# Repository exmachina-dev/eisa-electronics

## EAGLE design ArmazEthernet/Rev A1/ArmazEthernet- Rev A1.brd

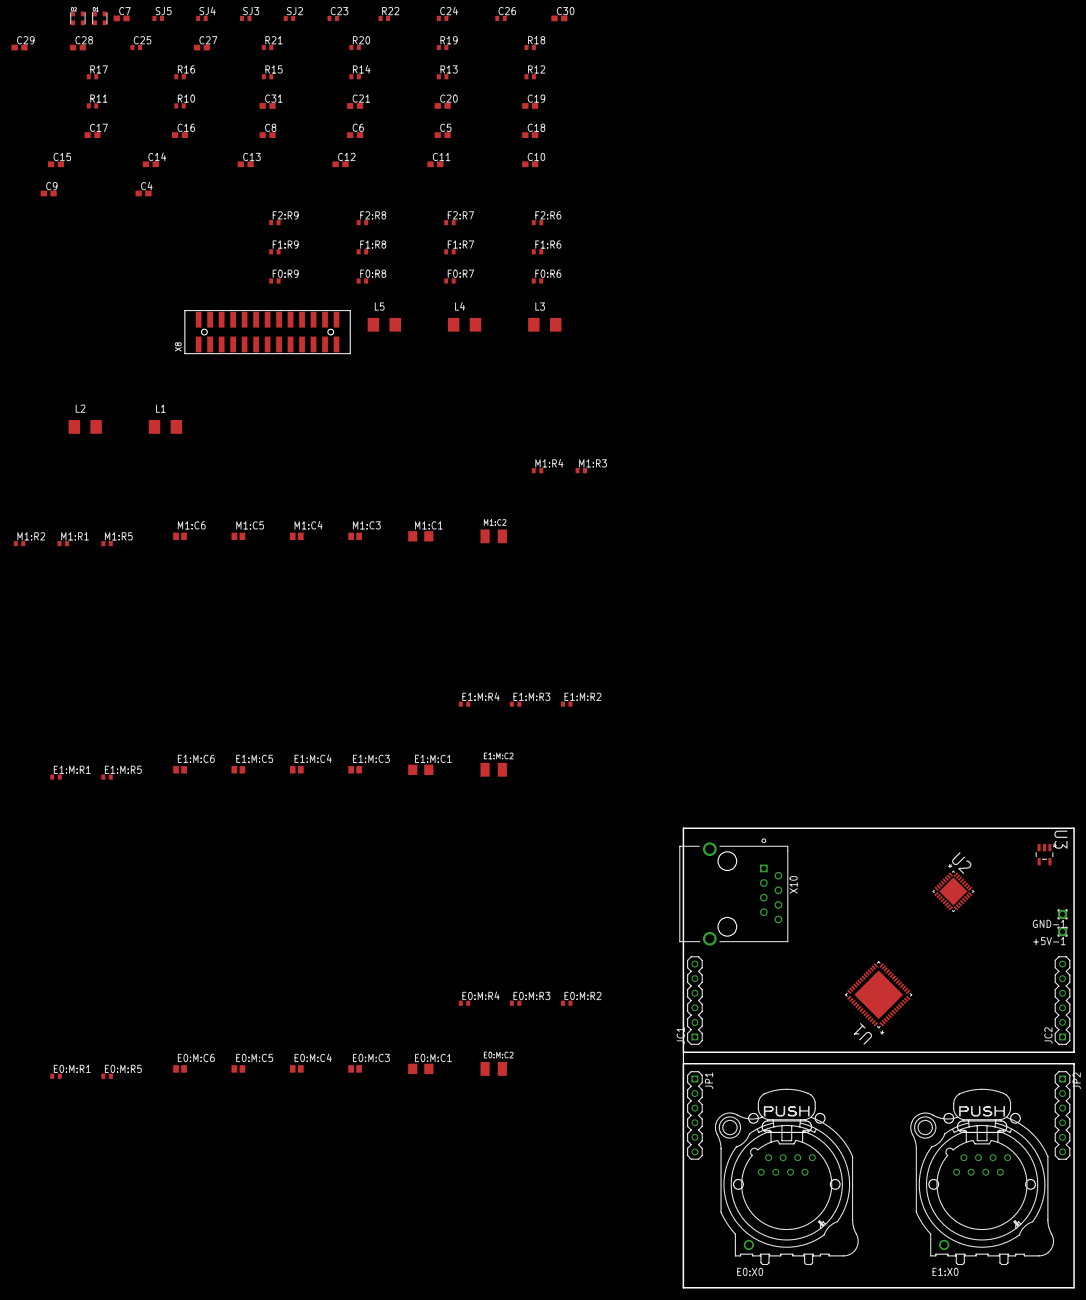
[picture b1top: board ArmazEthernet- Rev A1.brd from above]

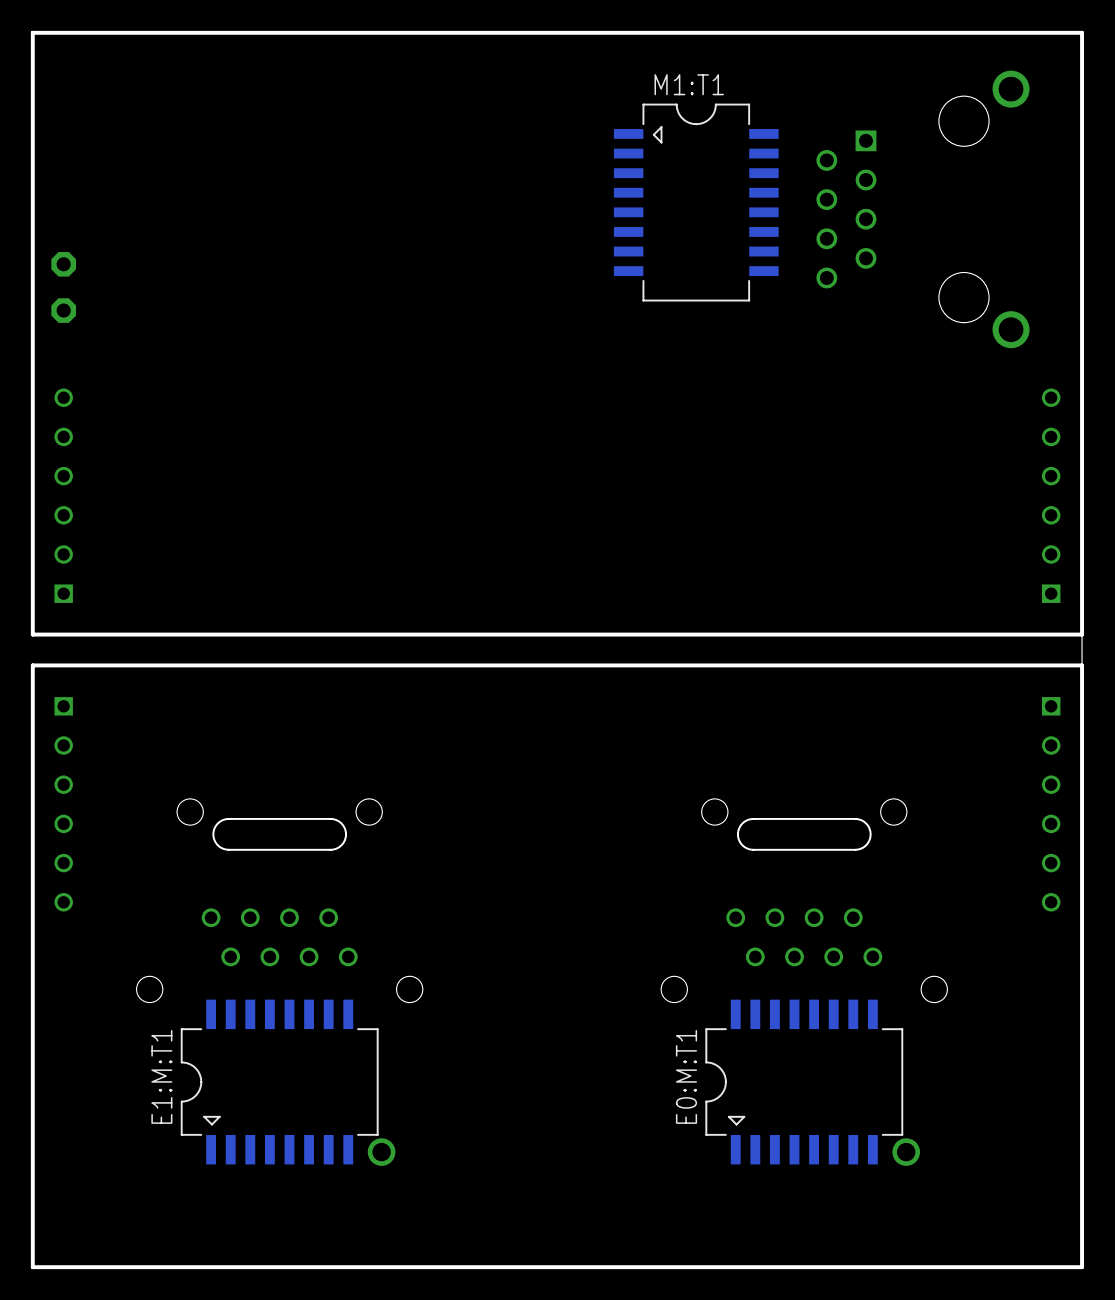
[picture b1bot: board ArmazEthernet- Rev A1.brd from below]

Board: 4 copper layers, 68.0 x 80.0 mm, 112 parts (3 on the bottom side), 92 nets, no tracks yet.

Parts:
+5V-1: WIREPAD1,6/0,9; 1,6/0,9
C4, C9, C10, C11, C12, C13, C14, C15, C18: 4.7uF, 6.3V, 20%; C0603
C5, C6, C8, C16, C17, C19, C20: 0.1uF, 16V, 10%; C0603
C7: 0.1uF; C0603
C21, C31: 0.01uF, 6V, 10%; C0603
C23: 1uF, 16V; C0402
C24: 10nF, 50V; C0402
C25: 4.7uF, 6.3V; C0402
C26: 0.1uF, 16V; C0402
C27: 4.7uF, 6.3V; C0603
C28, C29, C30: 0.1uF, 16V; C0603
E0:M:C1, E1:M:C1: 1000pF, 2kV; C1206
E0:M:C2, E1:M:C2: .022uF; SMC_B
E0:M:C3, E0:M:C4, E0:M:C5, E0:M:C6, E1:M:C3, E1:M:C4, E1:M:C5, E1:M:C6: 15pF, 50V; C0504
E0:M:R1, E0:M:R2, E0:M:R3, E0:M:R4, E1:M:R1, E1:M:R2, E1:M:R3, E1:M:R4: 75; R0402
E0:M:R5, E1:M:R5: 10, 1/8W, 1%; R0402
E0:M:T1, E1:M:T1: 749010012
E0:X0, E1:X0: NE8FAV
F0:R6, F0:R7, F0:R8, F0:R9, F1:R6, F1:R7, F1:R8, F1:R9, F2:R6, F2:R7, F2:R8, F2:R9: 49.9, 1/8W, 1%; R0402
GND-1: WIREPAD1,6/0,9; 1,6/0,9
JC1, JC2: 1X06
JP1, JP2: 1X06
L1, L2, L3, L4, L5: 2.0A/0.05 DCR; L4532M
M1:C1: 1000pF, 2kV; C1206
M1:C2: .022uF; SMC_B
M1:C3, M1:C4, M1:C5, M1:C6: 15pF, 50V; C0504
M1:R1, M1:R2, M1:R3, M1:R4: 75; R0402
M1:R5: 10, 1/8W, 1%; R0402
M1:T1: 749010012
O1, O2: 25MHz; ADSM
R10, R11, R12, R13, R14, R15, R16, R17, R18, R19, R20, R21: 10K, 1/10W, 1%; R0402
R22: 12K4, 1%; R0402
SJ2, SJ3, SJ4, SJ5: O, DNI; R0402
U1: LAN9303-ABZJ; QFN50P800X800X100-57N
U2: LAN8710AI-EZK; QFN50P500X500X100-33N
U3: LP2992IM5-3.3; SOT95P284X122-5N
X8: 87832-26
X10: 85505-5113; MOLEX_85505-5113

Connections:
+3V3: C4.1, C5.1, C6.1, C7.1, C8.1, C21.1, C25.1, C26.1, C31.1, L1.1, L2.1, L4.1, L5.1, O1.4, O2.4, R10.1, R12.1, R14.1, R16.1, R18.2, R19.2, R20.2, U1.9, U1.15, U1.23, U1.30, U1.32, U1.33, U3.5
+5V: +5V-1.1, C23.1, U3.1, U3.3, X8.1, X8.2
+12V: X8.21, X8.22
AVDD: C27.1, C28.1, C29.1, F2:R6.2, F2:R7.2, F2:R8.2, F2:R9.2, L5.2, M1:R5.2, U2.1, U2.27
DUPLEX_POL_0: R16.2, R17.1, SJ5.1
E0:M:N$1: E0:M:C2.+, E0:M:R5.1, E0:M:T1.2, E0:M:T1.7
E0:M:N$2: E0:M:R2.1, E0:M:T1.10
E0:M:N$3: E0:M:R4.1, E0:M:T1.15
E0:M:N$8: E0:M:C1.1, E0:M:R1.1, E0:M:R2.2, E0:M:R3.1, E0:M:R4.2
E0:N$1: E0:M:T1.11, E0:X0.1
E0:N$2: E0:M:T1.9, E0:X0.2
E0:N$3: E0:M:T1.16, E0:X0.3
E0:N$4: E0:M:T1.14, E0:X0.6
E0:N$5: E0:M:R1.2, E0:X0.4, E0:X0.5
E0:N$6: E0:M:R3.2, E0:X0.7, E0:X0.8
E1:M:N$1: E1:M:C2.+, E1:M:R5.1, E1:M:T1.2, E1:M:T1.7
E1:M:N$2: E1:M:R2.1, E1:M:T1.10
E1:M:N$3: E1:M:R4.1, E1:M:T1.15
E1:M:N$8: E1:M:C1.1, E1:M:R1.1, E1:M:R2.2, E1:M:R3.1, E1:M:R4.2
E1:N$1: E1:M:T1.11, E1:X0.1
E1:N$2: E1:M:T1.9, E1:X0.2
E1:N$3: E1:M:T1.16, E1:X0.3
E1:N$4: E1:M:T1.14, E1:X0.6
E1:N$5: E1:M:R1.2, E1:X0.4, E1:X0.5
E1:N$6: E1:M:R3.2, E1:X0.7, E1:X0.8
E2_1: M1:T1.11, X10.1
E2_2: M1:T1.9, X10.2
E2_3: M1:T1.16, X10.3
E2_4/5: M1:R1.2, X10.4, X10.5
E2_6: M1:T1.14, X10.6
E2_7/8: M1:R3.2, X10.7, X10.8
EE_SCL/SCL: R18.1, U1.36
EE_SDA/SDA: R19.1, U1.35
GND: C4.2, C5.2, C6.2, C7.2, C8.2, C9.2, C10.2, C11.2, C12.2, C13.2, C14.2, C15.2, C16.2, C17.2, C18.2, C19.2, C20.2, C21.2, C23.2, C24.2, C25.2, C26.2, C27.2, C28.2, C29.2, C30.2, C31.2, E0:M:C1.2, E0:M:C2.-, E0:M:C3.2, E0:M:C4.2, E0:M:C5.2, E0:M:C6.2, E0:X0.G, E1:M:C1.2, E1:M:C2.-, E1:M:C3.2, E1:M:C4.2, E1:M:C5.2, E1:M:C6.2, E1:X0.G, GND-1.1, JC1.6, JC2.6, JP1.6, JP2.6, M1:C1.2, M1:C2.-, M1:C3.2, M1:C4.2, M1:C5.2, M1:C6.2, O1.2, O2.2, R21.1, R22.1, SJ2.2, SJ3.2, SJ4.2, SJ5.2, U1.34, U1.57, U3.2, X8.3, X8.4, X10.M1, X10.M2
GND1: X8.25, X8.26
M1:N$1: M1:C2.+, M1:R5.1, M1:T1.2, M1:T1.7
M1:N$2: M1:R2.1, M1:T1.10
M1:N$3: M1:R4.1, M1:T1.15
M1:N$8: M1:C1.1, M1:R1.1, M1:R2.2, M1:R3.1, M1:R4.2
MDC: R21.2, U1.22, U2.17
MDIO: R20.1, U1.21, U2.16
unnamed: C24.1, U3.4
unnamed: R22.2, U1.49
unnamed: E0:M:C5.1, E0:M:T1.6, JP1.2
unnamed: E0:M:C6.1, E0:M:T1.8, JP1.3
unnamed: E0:M:C3.1, E0:M:T1.1, JP1.4
unnamed: E0:M:C4.1, E0:M:T1.3, JP1.5
unnamed: E1:M:R5.2, JP2.1
unnamed: E0:M:R5.2, JP1.1
unnamed: E1:M:C5.1, E1:M:T1.6, JP2.2
unnamed: E1:M:C6.1, E1:M:T1.8, JP2.3
unnamed: E1:M:C3.1, E1:M:T1.1, JP2.4
unnamed: E1:M:C4.1, E1:M:T1.3, JP2.5
P0_COL: U1.18, U2.15
P0_CRS: U1.19, U2.14
P0_INCLK: U1.8, U2.7
P0_IND0: U1.5, U2.11
P0_IND1: U1.4, U2.10
P0_IND2: U1.3, U2.9
P0_IND3: U1.2, U2.8
P0_INDV: U1.6, U2.26
P0_INER: U1.7, U2.13
P0_MODE0: R10.2, R11.1, SJ2.1
P0_MODE2: R14.2, R15.1, SJ4.1
P0_OUTCLK: U1.17, U2.20
P0_OUTD0/P0_MODE0: R11.2, U1.14, U2.22
P0_OUTD1/P0_MODE1: R13.2, U1.13
P0_OUTD2/P0_MODE2: R15.2, U1.12, U2.24
P0_OUTD3/DUPLEX_POL_0: R17.2, U1.11, U2.25
P0_OUTDV: U1.16, U2.21
PO_MODE1: R12.2, R13.1, SJ3.1
RXN0: F2:R9.1, M1:C4.1, M1:T1.3, U2.30
RXN1: F0:R9.1, JC1.5, U1.45
RXN2: F1:R9.1, JC2.5, U1.54
RXP0: F2:R8.1, M1:C3.1, M1:T1.1, U2.31
RXP1: F0:R8.1, JC1.4, U1.46
RXP2: F1:R8.1, JC2.4, U1.53
TXN0: F2:R7.1, M1:C6.1, M1:T1.8, U2.28
TXN1: F0:R7.1, JC1.3, U1.42
TXN2: F1:R7.1, JC2.3, U1.1
TXP0: F2:R6.1, M1:C5.1, M1:T1.6, U2.29
TXP1: F0:R6.1, JC1.2, U1.43
TXP2: F1:R6.1, JC2.2, U1.56
VDD18CORE: C15.1, C16.1, C17.1, L3.1, U1.10, U1.31
VDD18PLL: C13.1, L3.2, U1.41
VDD18TX: C18.1, C19.1, C20.1, U1.48, U1.51
VDD33A1: C9.1, C10.1, F0:R6.2, F0:R7.2, F0:R8.2, F0:R9.2, JC1.1, L1.2, U1.44, U1.47
VDD33A2: C11.1, C12.1, F1:R6.2, F1:R7.2, F1:R8.2, F1:R9.2, JC2.1, L2.2, U1.52, U1.55
VDD33BIAS: C14.1, L4.2, U1.50
VDDIO: C30.1, U2.12
XI: O1.3, U1.39
XTAL1/CLKIN: O2.3, U2.5

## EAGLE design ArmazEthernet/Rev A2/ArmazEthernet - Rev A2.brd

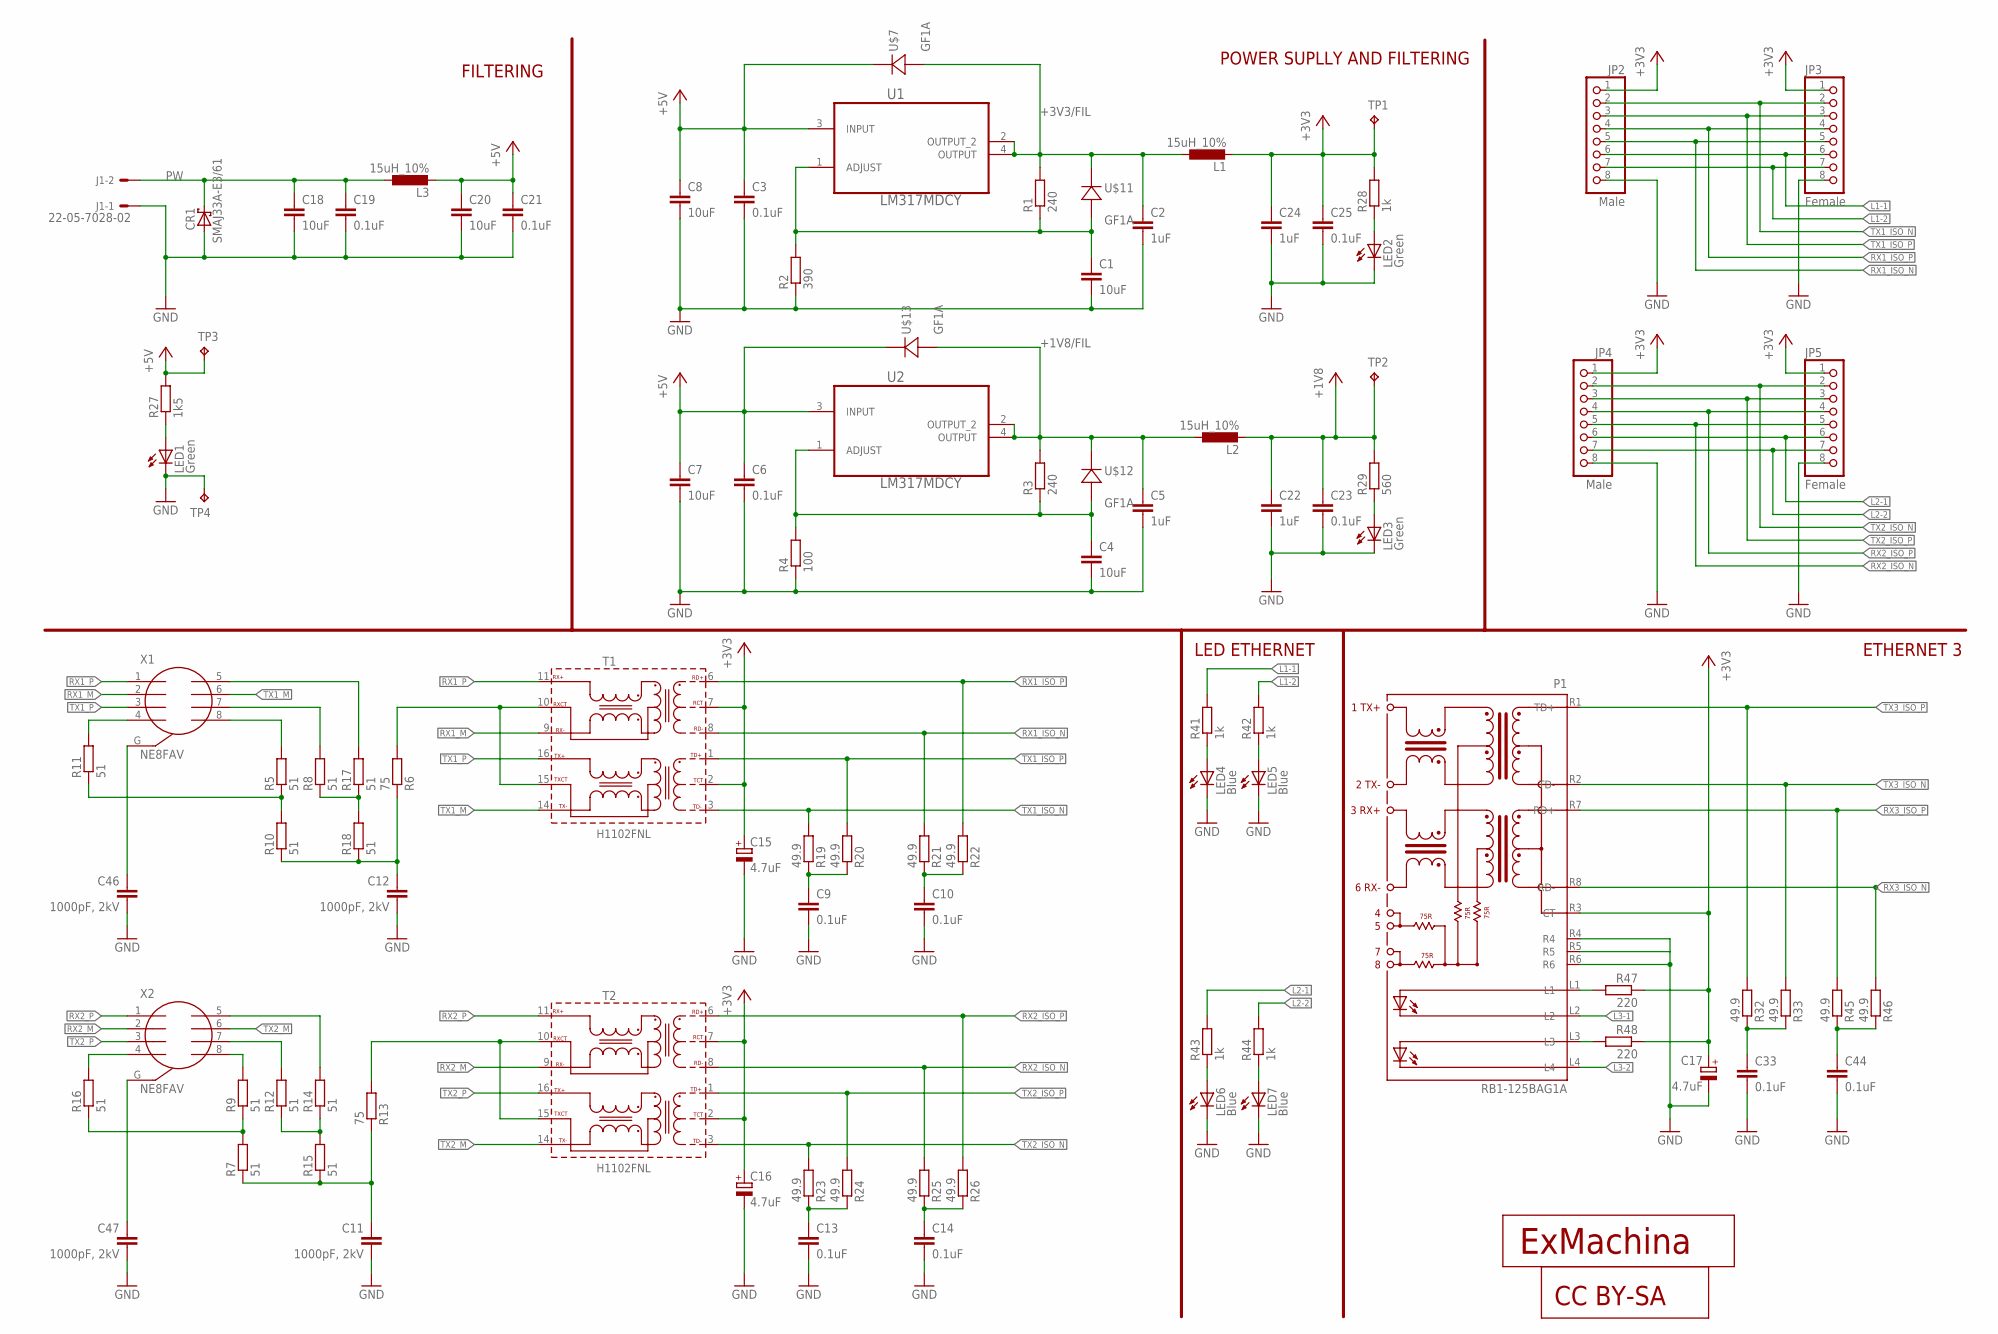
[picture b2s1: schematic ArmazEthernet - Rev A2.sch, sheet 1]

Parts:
C1, C4, C7, C8, C18, C20: 10uF; C0603; MPN MCNP16V106M5X11
C2, C5, C22, C24: 1uF; C0603; MPN MC0603B105K160CT
C3, C6, C9, C10, C13, C14, C19, C21, C23, C25, C33, C44: 0.1uF; C0603; MPN MC0603B104K160CT
C11, C12, C46, C47: 1000pF, 2kV; C1206; MPN MC1206B102K202CT
C15, C16, C17: 4.7uF; CT3216; MPN MCCTA475M010
CR1: SMAJ33A-E3/61; DIODE_DO-214AC; MPN SMAJ33A-E3/61
J1: 22-05-7028-02; 7395-02; MPN 22-05-7028
JP2, JP4: Male; 1X08; MPN 2211S-08G
JP3, JP5: Female; 1X08; MPN 2212S-08SG-85
L1, L2, L3: 15uH_10%; L4532M; MPN LQH43CN150K03L
LED1, LED2, LED3: Green; CHIP-LED0603; MPN OVS-0604
LED4, LED5, LED6, LED7: Blue; CHIP-LED0603; MPN OVS-0603
P1: RB1-125BAG1A; WIZNET_RB1-125BAG1A
R1, R3: 240; R0603; MPN MC0063W06031240R
R2: 390; R0603; MPN MC0063W06031390R
R4: 100; R0603; MPN MC0063W06031100R
R5, R7, R8, R9, R10, R11, R12, R14, R15, R16, R17, R18: 51; R0603; MPN MC0063W0603151R
R6, R13: 75; R0603; MPN MC0063W0603175R
R19, R20, R21, R22, R23, R24, R25, R26, R32, R33, R45, R46: 49.9; R0603; MPN MC0603SAF499JT5E
R27: 1k5; R0603; MPN MC0063W060311K5
R28, R41, R42, R43, R44: 1k; R0603; MPN MCMR06X1001FTL
R29: 560; R0603; MPN MCMR06X1501FTL
R47, R48: 220; R0603; MPN MC0063W06031220R
T1, T2: H1102FNL; HXXXX
TP1, TP2, TP3, TP4: TPB1,27; B1,27
U1, U2: LM317MDCY; SOT230P700X180-4N
U$5: EXMACHINA-LOGO-NAME; EXM-LOGO-BASELINE
U$6: CC-BY-SA
U$7, U$11, U$12, U$13: GF1A; DO-214BA; MPN GF1B-E3/67A
X1, X2: NE8FAV

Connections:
+1V8: C22.1, C23.1, L2.2, R29.2, TP2.TP; also elsewhere on the board
+1V8/FIL: C5.1, L2.1, R3.2, U2.2 (OUTPUT_2), U2.4 (OUTPUT), U$12.C (1), U$13.A (2)
+3V3: C15.+, C16.+, C17.+, C24.1, C25.1, JP2.1, JP3.1, JP4.1, JP5.1, L1.2, P1.R3 (CT), R28.2, R47.1, R48.1, T1.2 (TCT), T1.7 (RCT), T2.2 (TCT), T2.7 (RCT), TP1.TP; also elsewhere on the board
+3V3/FIL: C2.1, L1.1, R1.2, U1.2 (OUTPUT_2), U1.4 (OUTPUT), U$7.A (2), U$11.C (1)
+5V: C3.1, C6.1, C7.1, C8.1, C20.1, C21.1, L3.2, R27.2, TP3.TP, U1.3 (INPUT), U2.3 (INPUT), U$7.C (1), U$13.C (1)
GND: C1.2, C2.2, C3.2, C4.2, C5.2, C6.2, C7.2, C8.2, C9.2, C10.2, C11.2, C12.2, C13.2, C14.2, C15.-, C16.-, C17.-, C18.2, C19.2, C20.2, C21.2, C22.2, C23.2, C24.2, C25.2, C33.2, C44.2, C46.2, C47.2, CR1.2 (A), J1.1, JP2.8, JP3.8, JP4.8, JP5.8, LED1.C, LED2.C, LED3.C, LED4.C, LED5.C, LED6.C, LED7.C, P1.R4, P1.R5, P1.R6, R2.1, R4.1, TP4.TP; also elsewhere on the board
L1-1: JP2.6, JP3.6, R41.2; also elsewhere on the board
L1-2: JP2.7, JP3.7, R42.2; also elsewhere on the board
L2-1: JP4.6, JP5.6, R43.2; also elsewhere on the board
L2-2: JP4.7, JP5.7, R44.2; also elsewhere on the board
L3-1: P1.L2; also elsewhere on the board
L3-2: P1.L4; also elsewhere on the board
unnamed: R6.2, T1.10 (RXCT), T1.15 (TXCT)
unnamed: C1.1, R1.1, R2.2, U1.1 (ADJUST), U$11.A (2)
unnamed: R13.2, T2.10 (RXCT), T2.15 (TXCT)
unnamed: R9.2, X2.8
unnamed: C4.1, R3.1, R4.2, U2.1 (ADJUST), U$12.A (2)
unnamed: R11.2, X1.4
unnamed: R5.2, X1.8
unnamed: R8.2, X1.7
unnamed: C9.1, R19.1, R20.1
unnamed: R17.2, X1.5
unnamed: R12.2, X2.7
unnamed: C11.1, R7.1, R13.1, R15.1
unnamed: R5.1, R10.2, R11.1
unnamed: R16.2, X2.4
unnamed: R7.2, R9.1, R16.1
unnamed: R8.1, R17.1, R18.2
unnamed: R14.2, X2.5
unnamed: R12.1, R14.1, R15.2
unnamed: LED4.A, R41.1
unnamed: LED1.A, R27.1
unnamed: LED2.A, R28.1
unnamed: LED3.A, R29.1
unnamed: C33.1, R32.1, R33.1
unnamed: LED5.A, R42.1
unnamed: LED6.A, R43.1
unnamed: LED7.A, R44.1
unnamed: C44.1, R45.1, R46.1
unnamed: C12.1, R6.1, R10.1, R18.1
unnamed: C10.1, R21.1, R22.1
unnamed: P1.L3, R48.2
unnamed: P1.L1, R47.2
unnamed: C47.1, X2.G
unnamed: C46.1, X1.G
unnamed: C13.1, R23.1, R24.1
unnamed: C14.1, R25.1, R26.1
PW: C18.1, C19.1, CR1.1 (C), J1.2, L3.1
RX1_ISO_N: JP2.5, JP3.5, R21.2, T1.8 (RD-); also elsewhere on the board
RX1_ISO_P: JP2.4, JP3.4, R22.2, T1.6 (RD+); also elsewhere on the board
RX1_M: T1.9 (RX-), X1.2
RX1_P: T1.11 (RX+), X1.1
RX2_ISO_N: JP4.5, JP5.5, R25.2, T2.8 (RD-); also elsewhere on the board
RX2_ISO_P: JP4.4, JP5.4, R26.2, T2.6 (RD+); also elsewhere on the board
RX2_M: T2.9 (RX-), X2.2
RX2_P: T2.11 (RX+), X2.1
RX3_ISO_N: P1.R8 (RD-), R46.2; also elsewhere on the board
RX3_ISO_P: P1.R7 (RD+), R45.2; also elsewhere on the board
TX1_ISO_N: JP2.2, JP3.2, R19.2, T1.3 (TD-); also elsewhere on the board
TX1_ISO_P: JP2.3, JP3.3, R20.2, T1.1 (TD+); also elsewhere on the board
TX1_M: T1.14 (TX-), X1.6
TX1_P: T1.16 (TX+), X1.3
TX2_ISO_N: JP4.2, JP5.2, R23.2, T2.3 (TD-); also elsewhere on the board
TX2_ISO_P: JP4.3, JP5.3, R24.2, T2.1 (TD+); also elsewhere on the board
TX2_M: T2.14 (TX-), X2.6
TX2_P: T2.16 (TX+), X2.3
TX3_ISO_N: P1.R2 (TD-), R33.2; also elsewhere on the board
TX3_ISO_P: P1.R1 (TD+), R32.2; also elsewhere on the board

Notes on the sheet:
FILTERING
POWER SUPLLY AND FILTERING
LED ETHERNET
ETHERNET 3

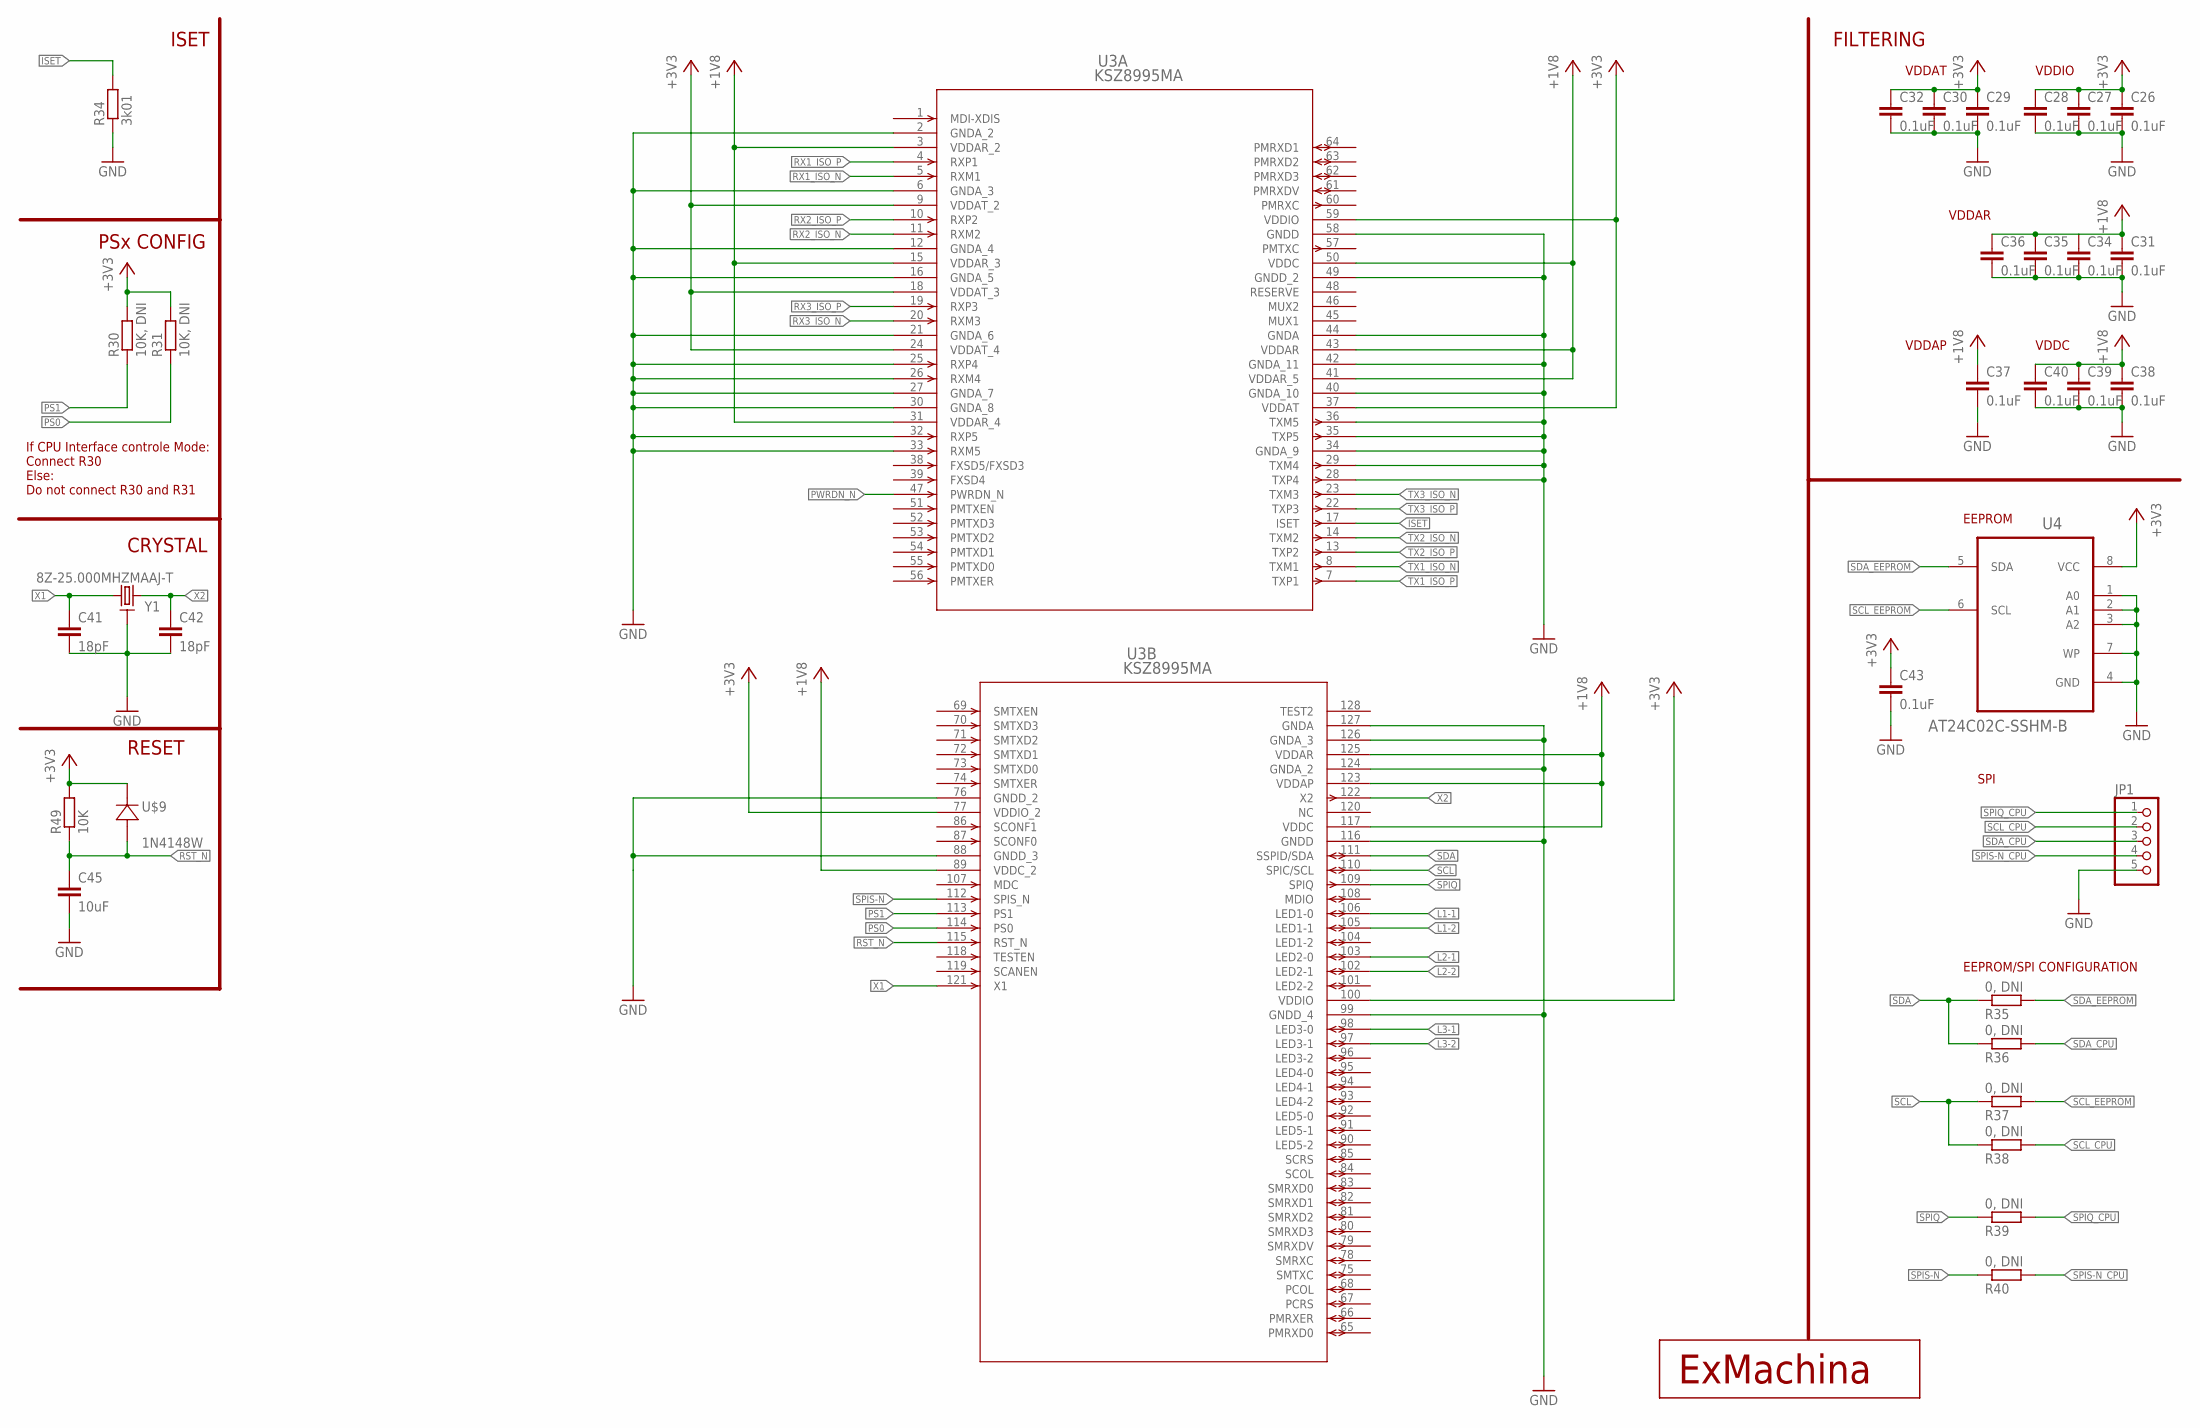
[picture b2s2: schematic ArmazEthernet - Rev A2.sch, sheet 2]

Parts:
C26, C27, C28, C29, C30, C31, C32, C34, C35, C36, C37, C38, C39, C40, C43: 0.1uF; C0603; MPN MC0603B104K160CT
C41, C42: 18pF; C0603; MPN MC0603N180J500CT
C45: 10uF; C0603; MPN MCNP16V106M5X11
JP1: PINHD-1X5; 1X05; MPN M20-9990545
R30, R31: 10K, DNI; R0603; MPN MC0063W0603110K
R34: 3k01; R0603; MPN MC0063W060313K01
R35, R36, R37, R38, R39, R40: 0, DNI; R0603; MPN MC0603WG00000T5E-TC
R49: 10K; R0603; MPN MC0063W0603110K
U3: KSZ8995MA; PQFP-128_MQL; MPN KSZ8995MA
U4: AT24C02C-SSHM-B; SOIC127P600X175-8N
U$8: EXMACHINA-LOGO-NAME; EXM-LOGO-BASELINE
U$9: 1N4148W; SOD-123_MINI-SMA; MPN 1N4148W
Y1: 8Z-25.000MHZMAAJ-T; SMD2.5X2; MPN 8Z-25.000MAAJ-T

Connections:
+1V8: C31.1, C34.1, C35.1, C36.1, C37.1, C38.1, C39.1, C40.1, U3.3 (VDDAR_2), U3.15 (VDDAR_3), U3.31 (VDDAR_4), U3.41 (VDDAR_5), U3.43 (VDDAR), U3.50 (VDDC), U3.89 (VDDC_2), U3.117 (VDDC), U3.123 (VDDAP), U3.125 (VDDAR); also elsewhere on the board
+3V3: C26.1, C27.1, C28.1, C29.1, C30.1, C32.1, C43.1, R30.2, R31.2, R49.2, U3.9 (VDDAT_2), U3.18 (VDDAT_3), U3.24 (VDDAT_4), U3.37 (VDDAT), U3.59 (VDDIO), U3.77 (VDDIO_2), U3.100 (VDDIO), U4.8 (VCC), U$9.C (1); also elsewhere on the board
GND: C26.2, C27.2, C28.2, C29.2, C30.2, C31.2, C32.2, C34.2, C35.2, C36.2, C37.2, C38.2, C39.2, C40.2, C41.2, C42.2, C43.2, C45.2, JP1.5, R34.1, U3.2 (GNDA_2), U3.6 (GNDA_3), U3.12 (GNDA_4), U3.16 (GNDA_5), U3.21 (GNDA_6), U3.25 (RXP4), U3.26 (RXM4), U3.27 (GNDA_7), U3.28 (TXP4), U3.29 (TXM4), U3.30 (GNDA_8), U3.32 (RXP5), U3.33 (RXM5), U3.34 (GNDA_9), U3.35 (TXP5), U3.36 (TXM5), U3.40 (GNDA_10), U3.42 (GNDA_11), U3.44 (GNDA), U3.49 (GNDD_2), U3.58 (GNDD), U3.76 (GNDD_2), U3.88 (GNDD_3), U3.99 (GNDD_4), U3.116 (GNDD), U3.124 (GNDA_2), U3.126 (GNDA_3), U3.127 (GNDA), U4.1 (A0), U4.2 (A1), U4.3 (A2), U4.4 (GND), U4.7 (WP), Y1.2, Y1.4 (2); also elsewhere on the board
ISET: R34.2, U3.17 (ISET)
L1-1: U3.106 (LED1-0); also elsewhere on the board
L1-2: U3.105 (LED1-1); also elsewhere on the board
L2-1: U3.103 (LED2-0); also elsewhere on the board
L2-2: U3.102 (LED2-1); also elsewhere on the board
L3-1: U3.98 (LED3-0); also elsewhere on the board
L3-2: U3.97 (LED3-1); also elsewhere on the board
PS0: R31.1, U3.114 (PS0)
PS1: R30.1, U3.113 (PS1)
PWRDN_N: U3.47 (PWRDN_N)
RST_N: C45.1, R49.1, U3.115 (RST_N), U$9.A (2)
RX1_ISO_N: U3.5 (RXM1); also elsewhere on the board
RX1_ISO_P: U3.4 (RXP1); also elsewhere on the board
RX2_ISO_N: U3.11 (RXM2); also elsewhere on the board
RX2_ISO_P: U3.10 (RXP2); also elsewhere on the board
RX3_ISO_N: U3.20 (RXM3); also elsewhere on the board
RX3_ISO_P: U3.19 (RXP3); also elsewhere on the board
SCL: R37.1, R38.1, U3.110 (SPIC/SCL)
SCL_CPU: JP1.2, R38.2
SCL_EEPROM: R37.2, U4.6 (SCL)
SDA: R35.1, R36.1, U3.111 (SSPID/SDA)
SDA_CPU: JP1.3, R36.2
SDA_EEPROM: R35.2, U4.5 (SDA)
SPIQ: R39.1, U3.109 (SPIQ)
SPIQ_CPU: JP1.1, R39.2
SPIS-N: R40.1, U3.112 (SPIS_N)
SPIS-N_CPU: JP1.4, R40.2
TX1_ISO_N: U3.8 (TXM1); also elsewhere on the board
TX1_ISO_P: U3.7 (TXP1); also elsewhere on the board
TX2_ISO_N: U3.14 (TXM2); also elsewhere on the board
TX2_ISO_P: U3.13 (TXP2); also elsewhere on the board
TX3_ISO_N: U3.23 (TXM3); also elsewhere on the board
TX3_ISO_P: U3.22 (TXP3); also elsewhere on the board
X1: C41.1, U3.121 (X1), Y1.1
X2: C42.1, U3.122 (X2), Y1.3

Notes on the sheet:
ISET
FILTERING
VDDIO
VDDAT
VDDAR
VDDC
VDDAP
PSx CONFIG
If CPU Interface controle Mode: Connect R30 Else: Do not connect R30 and R31
CRYSTAL
EEPROM
SPI
EEPROM/SPI CONFIGURATION
RESET

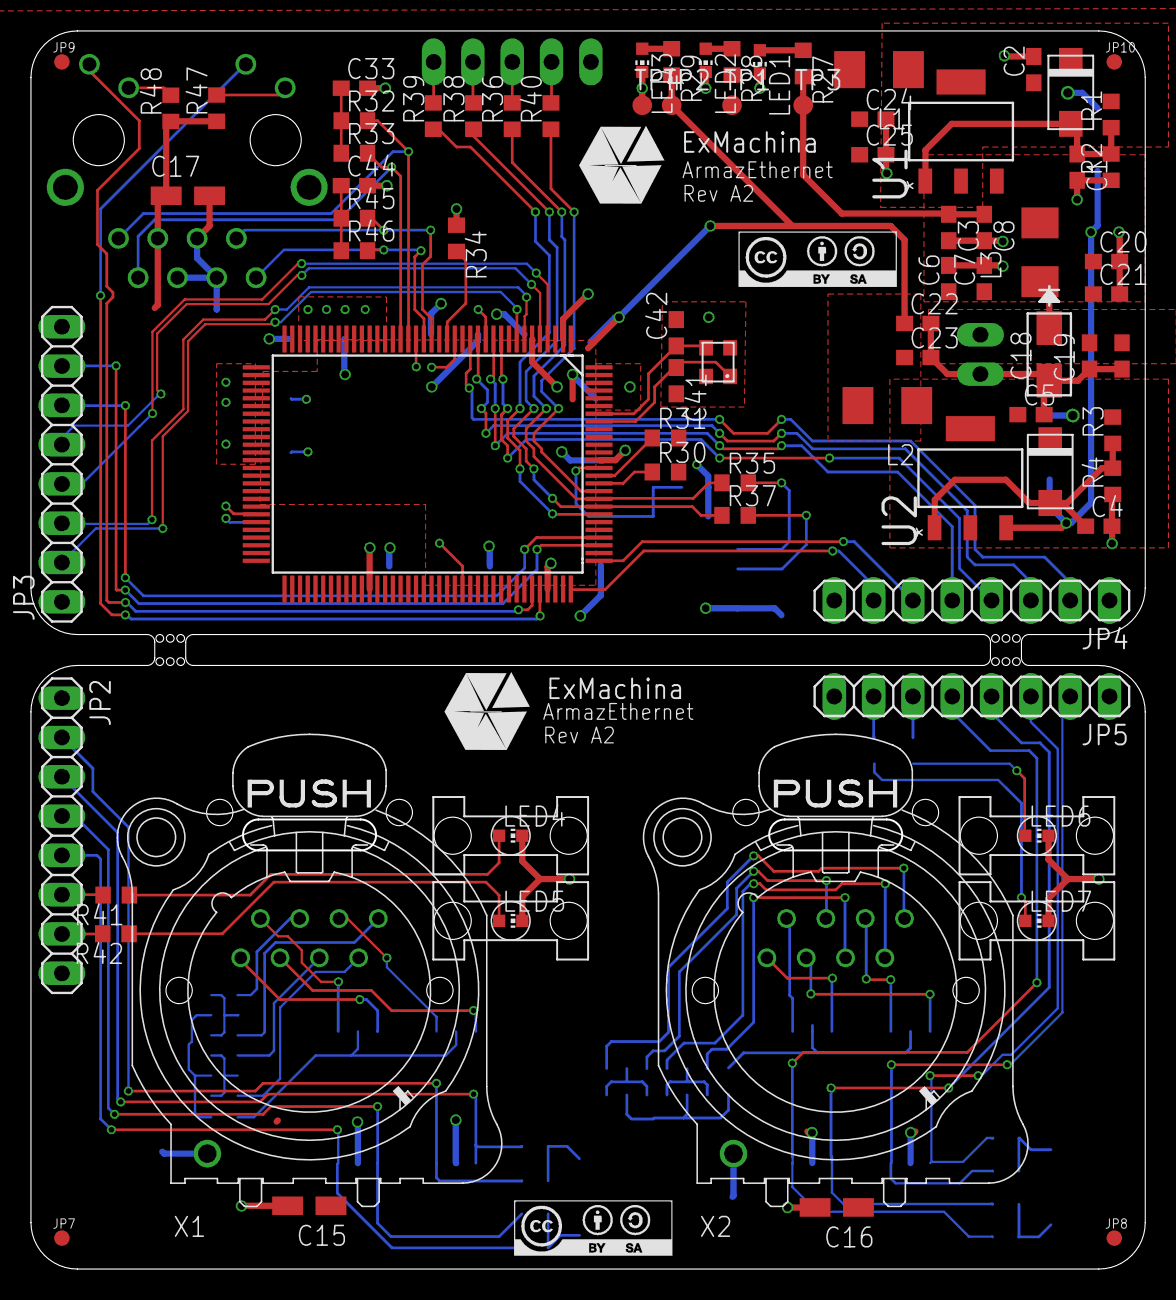
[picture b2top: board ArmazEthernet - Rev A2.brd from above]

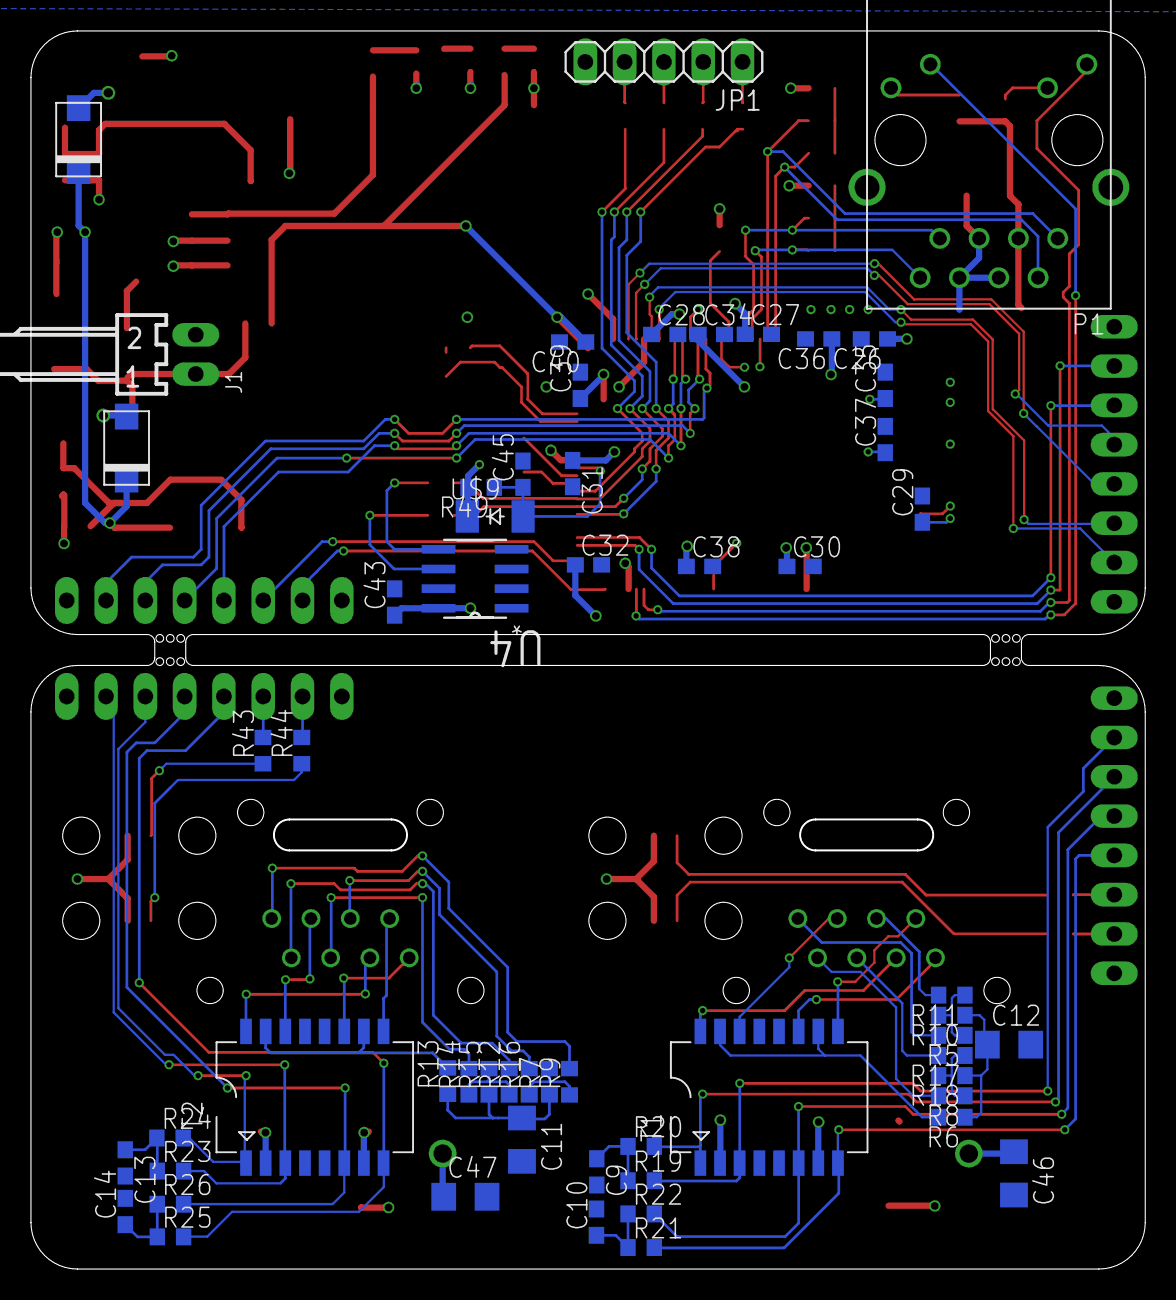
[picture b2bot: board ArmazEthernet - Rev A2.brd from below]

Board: 2 copper layers, 72.0 x 80.0 mm, 144 parts (58 on the bottom side), 84 nets.

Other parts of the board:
JP7, JP8, JP9, JP10: FIDUCIAL1X2; FIDUCIAL-1X2
U$1, U$2, U$3, U$4: 1275.100
U$10: CC-BY-SA

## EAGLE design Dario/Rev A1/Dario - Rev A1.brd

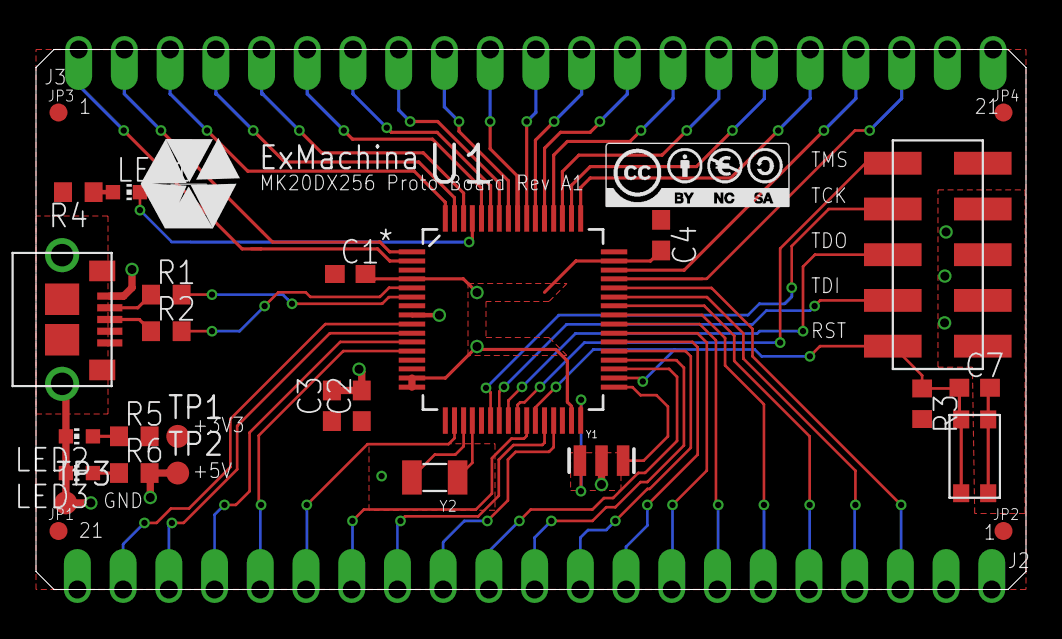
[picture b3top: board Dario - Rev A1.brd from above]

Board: 2 copper layers, 55.0 x 30.0 mm, 31 parts (0 on the bottom side), 57 nets.

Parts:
C1, C2, C3, C4, C7: 0.1uF; C0603
J1: 1241050-5; 2.54/2X5
J2, J3: 21_PIN; 21_CUSTOM
JP1, JP2, JP3, JP4: FIDUCIAL1X2; FIDUCIAL-1X2
LED1, LED2, LED3: CHIP-LED0603
R1, R2: 33; R0603
R3: 10k; R0603
R4, R5: 1k; R0603
R6: 1k5; R0603
SW1: KMR211G; KM_SERIE
TP1, TP2, TP3: TPB1,27; B1,27
U1: MK20DX256VLH7; QFP50P1200X1200X160-64N
U$1: USB3075-30-A; USB_MICROB_SMT
U$3: EXMACHINA-LOGO-NAME; EXM-LOGO-BASELINE
U$4: CC-BY-NC-SA
Y1: 8MHz; RESONATOR-SMD
Y2: 32.768kHz, 12.5pF; ABS07

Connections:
+3V3: C1.1, C2.1, C3.1, C4.1, J1.1, J2.P$1, J3.P$21, R3.2, R4.2, R5.2, TP1.TP, U1.3, U1.7, U1.13, U1.14, U1.17, U1.30, U1.48
+5V: J2.P$21, R6.2, TP2.TP, U1.8, U$1.1
DAC0_OUT: J2.P$16, U1.18
GND: C1.2, C2.2, C3.2, C4.2, C7.2, J1.3, J1.5, J1.7, J1.9, J2.P$2, J3.P$20, LED2.C, LED3.C, SW1.1, SW1.2, TP3.TP, U1.4, U1.15, U1.16, U1.31, U1.47, U$1.5, U$1.7, U$1.8, U$1.9, U$1.10, U$1.11, U$1.12, Y1.2
unnamed: R1.1, U$1.2
unnamed: R2.1, U$1.3
unnamed: U1.33, Y1.3
unnamed: U1.32, Y1.1
unnamed: U1.19, Y2.2
unnamed: U1.20, Y2.1
unnamed: LED1.C, U1.61
unnamed: LED1.A, R4.1
unnamed: LED3.A, R6.1
unnamed: LED2.A, R5.1
PGA0_N: J2.P$19, U1.10
PGA0_P: J2.P$20, U1.9
PGA1_N: J2.P$17, U1.12
PGA1_P: J2.P$18, U1.11
PTA4: J2.P$15, U1.26
PTA12: J2.P$14, U1.28
PTA13: J2.P$13, U1.29
PTB0: J2.P$12, U1.35
PTB1: J2.P$11, U1.36
PTB2: J2.P$10, U1.37
PTB3: J2.P$9, U1.38
PTB16: J2.P$8, U1.39
PTB17: J2.P$7, U1.40
PTB18: J2.P$6, U1.41
PTB19: J2.P$5, U1.42
PTC0: J2.P$4, U1.43
PTC1: J2.P$3, U1.44
PTC2: J3.P$19, U1.45
PTC3: J3.P$18, U1.46
PTC4: J3.P$17, U1.49
PTC5: J3.P$16, U1.50
PTC6: J3.P$15, U1.51
PTC7: J3.P$14, U1.52
PTC8: J3.P$13, U1.53
PTC9: J3.P$12, U1.54
PTC10: J3.P$11, U1.55
PTC11: J3.P$10, U1.56
PTD0: J3.P$9, U1.57
PTD1: J3.P$8, U1.58
PTD2: J3.P$7, U1.59
PTD3: J3.P$6, U1.60
PTD5: J3.P$5, U1.62
PTD6: J3.P$4, U1.63
PTD7: J3.P$3, U1.64
PTE0: J3.P$2, U1.1
PTE1: J3.P$1, U1.2
RESET: C7.1, J1.10, R3.1, SW1.3, SW1.4, U1.27, U1.34
TCK/SWDCLK: J1.4, U1.22
TDI: J1.8, U1.23
TDO: J1.6, U1.24
TMS/SWDIO: J1.2, U1.25
USB_N: R1.2, U1.6
USB_P: R2.2, U1.5

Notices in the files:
parts and their libraries:
COPYRIGHT: Copyright (C) 2015 Accelerated Designs. All rights reserved
